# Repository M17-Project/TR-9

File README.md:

# TR-9
<p align='center'>

</p>

TR-9 is a handheld transceiver (HT) for the M17 standard. Its specification can be found [here](https://github.com/sp5wwp/M17_spec).
This repo contains KiCAD schematics and gerber files. 

The firmware source code has been moved to [M17-project/TR-9_firmware](https://github.com/m17-project/TR-9_firmware).
The codeplug example has been moved to [TR-9_Codeplug](https://github.com/M17-Project/codeplug)

# Capabilities
The TR-9 Radio will be capable of the following:
* UHF band (420 MHz - 450 MHz)
* Digital Voice ([M17 Codec](https://docs.m17project.org))
* FM Voice
* APRS via 1200 bps Packet (AX.25)
* Short text messaging (SMS-like)
* Optional Wi-Fi and GPS modules

# Hardware  
The heart of TR-9 is STM32F777VI microcontroller. The handheld also contains:  
*  a **DEM 128128A1 TMH-PWN** 1.44" 128x128px TFT display  
*  an **ESP8266-12F** WiFi module  
*  an **ADF7021** chip for the RF  
*  an **LSM9DS1** 9DoF sensor  
*  a USB-micro connector for firmware update (so-called *DFU mode*)  
*  a microSD card slot for codeplug and storage  
*  a connector for a GNSS module  
*  a Kenwood connector for external MIC/SPK  

RF output level can be regulated by the software. The maximum power output is 3 watts. The radio can work with both analog and digital modulation.  

# Software
M17 standard was designed having [Codec2](https://github.com/drowe67/codec2) vocoder in mind. TR-9 takes advantage of STM's internal Advanced Encryption Standard (AES) hardware for optional end-to-end encryption. There is a possibility of using other block ciphers and scrambling.  

## Pinouts

Mainboard SWD/STLink: [GND, 3v3, CLK, DIO, RST], square pad is Pin 1 and therefore GND.

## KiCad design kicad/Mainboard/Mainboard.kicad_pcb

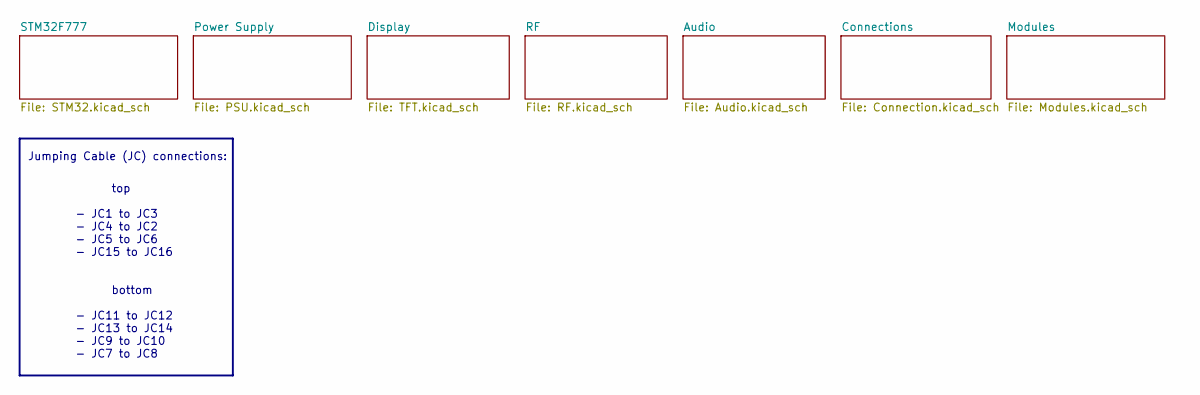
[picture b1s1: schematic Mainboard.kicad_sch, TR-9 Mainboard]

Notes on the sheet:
top - JC1 to JC3 - JC4 to JC2 - JC5 to JC6 - JC15 to JC16 bottom - JC11 to JC12 - JC13 to JC14 - JC9 to JC10 - JC7 to JC8
Jumping Cable (JC) connections:

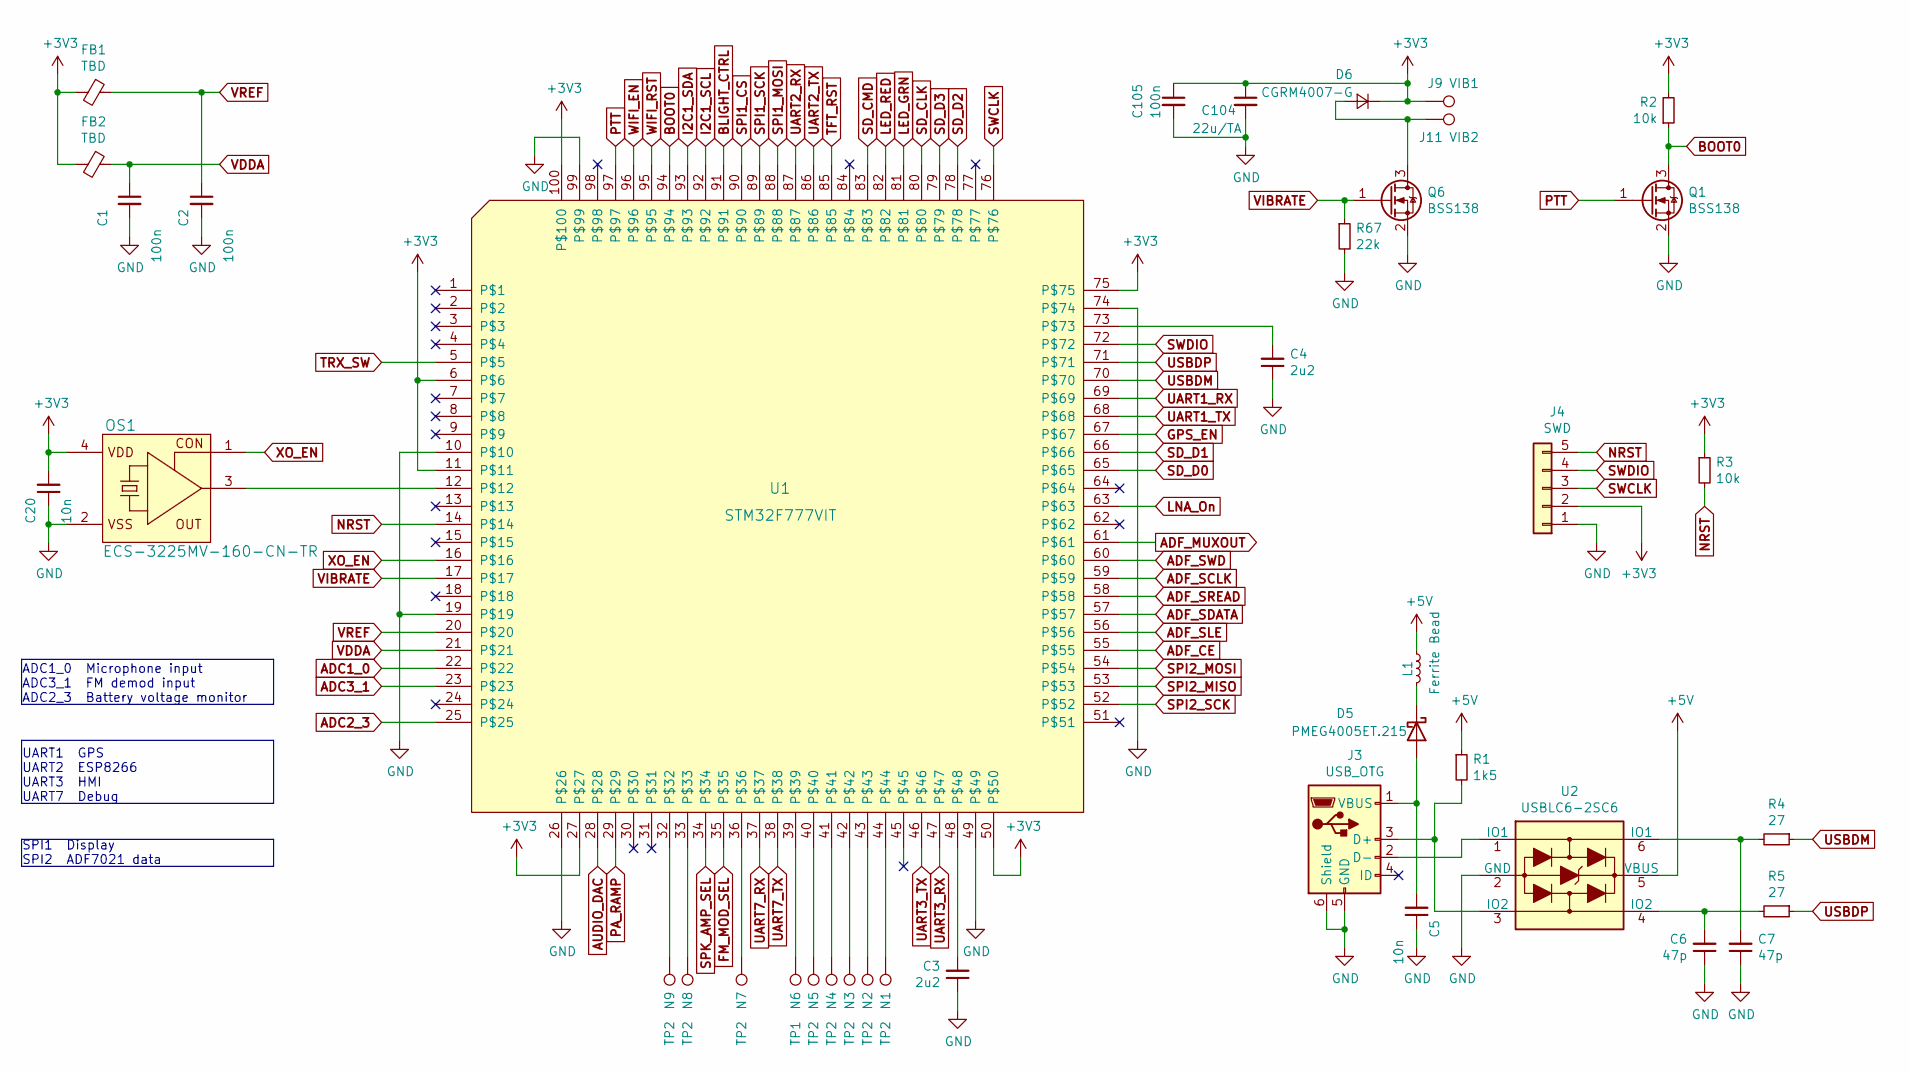
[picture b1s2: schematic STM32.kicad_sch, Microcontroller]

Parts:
C1, C2, C105: 100n; C_0603_1608Metric; Voltage 50; Tolerance 10
C3, C4: 2u2; C_0603_1608Metric; Tolerance 10; Voltage 50
C5: 10n; C_0603_1608Metric; Voltage 50; Tolerance 10
C6, C7: 47p; C_0603_1608Metric; Tolerance 5; Voltage 50
C20: 10n; C_0603_1608Metric; Tolerance 10; Voltage 50
C104: 22u/TA; CP_EIA-3216-18_Kemet-A; Tolerance 10; Voltage 10; Partno TAJA226K006RNJV
D5: PMEG4005ET.215
D6: CGRM4007-G; D_SOD-123
FB1, FB2: TBD; L_0603_1608Metric
J3: USB_OTG; USB_Mini-B_Wuerth_65100516121_Horizontal
J4: SWD; PinHeader_1x05_P1.27mm_Vertical
J9: VIB1; TestPoint_Pad_2.0x2.0mm
J11: VIB2; TestPoint_Pad_2.0x2.0mm
L1: Ferrite Bead; L_0603_1608Metric; Partno Fair-Rite 2506032217Y2
N1, N2, N3, N4, N5, N7, N8, N9: TP2; TestPoint_Pad_D1.0mm
N6: TP1; TestPoint_Pad_D1.0mm
OS1: ECS-3225MV-160-CN-TR; ECS-3225-MV-160-CN-TR
Q1, Q6: BSS138; SOT-23
R1: 1k5; R_0603_1608Metric; Tolerance 5
R2, R3: 10k; R_0603_1608Metric; Tolerance 5
R4, R5: 27; R_0603_1608Metric; Tolerance 5
R67: 22k; R_0603_1608Metric; Tolerance 5
U1: STM32F777VIT; LQFP-100_14x14mm_P0.5mm
U2: USBLC6-2SC6; SOT-23-6

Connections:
+5V: L1.1, R1.1, U2.5 (VBUS); also elsewhere on the board
ADC1_0: U1.22; also elsewhere on the board
ADC2_3: U1.25; also elsewhere on the board
ADC3_1: U1.23; also elsewhere on the board
ADF_CE: U1.55; also elsewhere on the board
ADF_MUXOUT: U1.61; also elsewhere on the board
ADF_SCLK: U1.59; also elsewhere on the board
ADF_SDATA: U1.57; also elsewhere on the board
ADF_SLE: U1.56; also elsewhere on the board
ADF_SREAD: U1.58; also elsewhere on the board
ADF_SWD: U1.60; also elsewhere on the board
AUDIO_DAC: U1.28; also elsewhere on the board
BLIGHT_CTRL: U1.91; also elsewhere on the board
BOOT0: Q1.3 (D), R2.1, U1.94
FM_MOD_SEL: U1.35; also elsewhere on the board
GPS_EN: U1.67; also elsewhere on the board
I2C1_SCL: U1.92; also elsewhere on the board
I2C1_SDA: U1.93; also elsewhere on the board
LED_GRN: U1.81; also elsewhere on the board
LED_RED: U1.82; also elsewhere on the board
LNA_On: U1.63; also elsewhere on the board
NRST: J4.5, R3.2, U1.14
unnamed: C3.2, U1.48
unnamed: C4.2, U1.73
unnamed: C5.2, D5.2 (A), J3.1 (VBUS)
unnamed: C6.2, R5.2, U2.4 (IO2)
unnamed: C7.2, R4.2, U2.6 (IO1)
unnamed: D5.1 (K), L1.2
unnamed: D6.2 (A), J11.1, Q6.3 (D)
unnamed: J3.2 (D-), U2.1 (IO1)
unnamed: J3.3 (D+), R1.2, U2.3 (IO2)
unnamed: N1.1, U1.44
unnamed: N2.1, U1.43
unnamed: N3.1, U1.42
unnamed: N4.1, U1.41
unnamed: N5.1, U1.40
unnamed: N6.1, U1.39
unnamed: N7.1, U1.36
unnamed: N8.1, U1.33
unnamed: N9.1, U1.32
unnamed: OS1.3 (OUT), U1.12
PA_RAMP: U1.29; also elsewhere on the board
PTT: Q1.1 (G), U1.97; also elsewhere on the board
SD_CLK: U1.80; also elsewhere on the board
SD_CMD: U1.83; also elsewhere on the board
SD_D0: U1.65; also elsewhere on the board
SD_D1: U1.66; also elsewhere on the board
SD_D2: U1.78; also elsewhere on the board
SD_D3: U1.79; also elsewhere on the board
SPI1_CS: U1.90; also elsewhere on the board
SPI1_MOSI: U1.88; also elsewhere on the board
SPI1_SCK: U1.89; also elsewhere on the board
SPI2_MISO: U1.53; also elsewhere on the board
SPI2_MOSI: U1.54; also elsewhere on the board
SPI2_SCK: U1.52; also elsewhere on the board
SPK_AMP_SEL: U1.34; also elsewhere on the board
SWCLK: J4.3, U1.76
SWDIO: J4.4, U1.72
TFT_RST: U1.85; also elsewhere on the board
TRX_SW: U1.5; also elsewhere on the board
UART1_RX: U1.69; also elsewhere on the board
UART1_TX: U1.68; also elsewhere on the board
UART2_RX: U1.87; also elsewhere on the board
UART2_TX: U1.86; also elsewhere on the board
UART3_RX: U1.47; also elsewhere on the board
UART3_TX: U1.46
UART7_RX: U1.37; also elsewhere on the board
UART7_TX: U1.38; also elsewhere on the board
USBDM: R4.1, U1.70
USBDP: R5.1, U1.71
VDDA: C1.1, FB2.1, U1.21
VIBRATE: Q6.1 (G), R67.1, U1.17
VREF: C2.1, FB1.1, U1.20
WIFI_EN: U1.96; also elsewhere on the board
WIFI_RST: U1.95; also elsewhere on the board
XO_EN: OS1.1 (CON), U1.16

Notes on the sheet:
UART1 GPS UART2 ESP8266 UART3 HMI UART7 Debug
ADC1_0 Microphone input ADC3_1 FM demod input ADC2_3 Battery voltage monitor
SPI1 Display SPI2 ADF7021 data

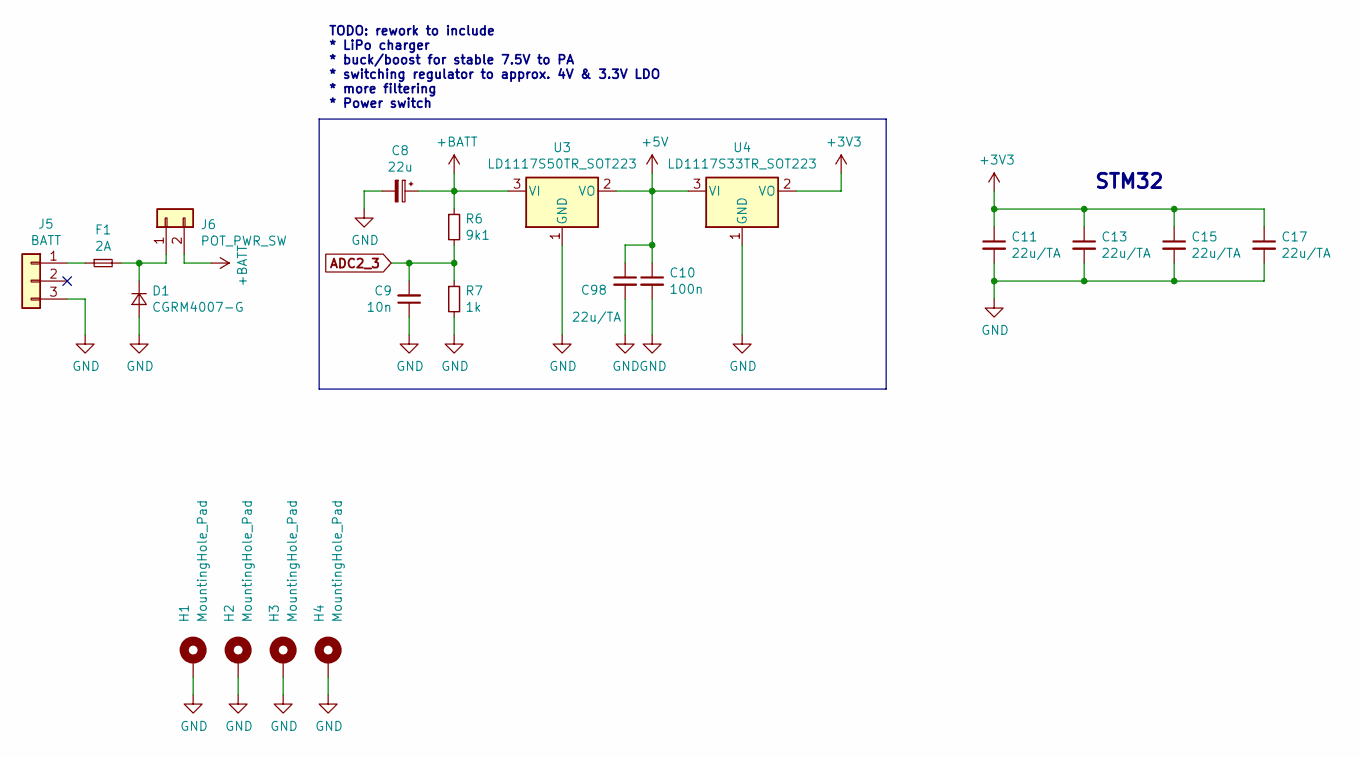
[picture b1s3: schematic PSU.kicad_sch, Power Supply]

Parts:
C8: 22u; CP_Radial_D4.0mm_P2.00mm; Tolerance 10; Voltage 25; Partno TAJA226K006RNJV
C9: 10n; C_0603_1608Metric; Tolerance 10; Voltage 50
C10: 100n; C_0603_1608Metric; Voltage 50; Tolerance 10
C11, C13, C15, C17, C98: 22u/TA; CP_EIA-3216-18_Kemet-A; Tolerance 10; Voltage 10; Partno TAJA226K006RNJV
D1: CGRM4007-G; D_SOD-123
F1: 2A; Fuse_1812_4532Metric
H1, H2, H3, H4: MountingHole_Pad; MountingHole_2.2mm_M2_ISO14580_Pad
J5: BATT; PinHeader_1x03_P1.27mm_Vertical
J6: POT_PWR_SW; PinHeader_1x02_P1.27mm_Vertical
R6: 9k1; R_0603_1608Metric; Tolerance 5
R7: 1k; R_0603_1608Metric; Tolerance 5
U3: LD1117S50TR_SOT223; SOT-223-3_TabPin2
U4: LD1117S33TR_SOT223; SOT-223-3_TabPin2

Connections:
+5V: C10.1, C98.1, U3.2 (VO), U4.3 (VI); also elsewhere on the board
+BATT: C8.1, J6.2, R6.1, U3.3 (VI); also elsewhere on the board
ADC2_3: C9.2, R6.2, R7.1; also elsewhere on the board
unnamed: D1.1 (K), F1.2, J6.1
unnamed: F1.1, J5.1

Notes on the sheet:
STM32
TODO: rework to include * LiPo charger * buck/boost for stable 7.5V to PA * switching regulator to approx. 4V & 3.3V LDO * more filtering * Power switch

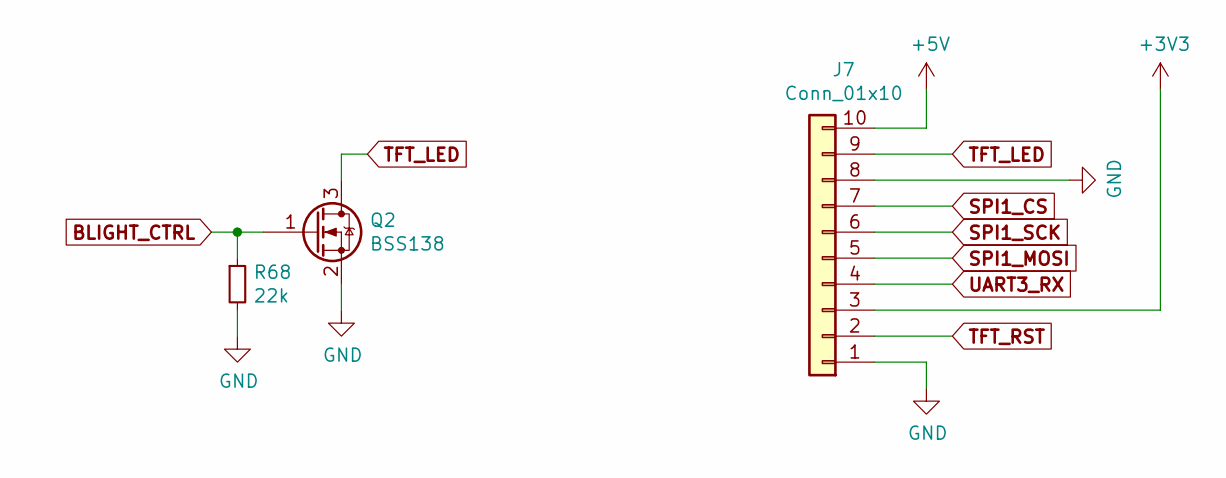
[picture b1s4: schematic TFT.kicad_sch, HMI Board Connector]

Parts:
J7: Conn_01x10; Hirose_FH12-10S-0.5SH_1x10-1MP_P0.50mm_Horizontal
Q2: BSS138; SOT-23
R68: 22k; R_0603_1608Metric; Tolerance 5

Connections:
+5V: J7.10; also elsewhere on the board
BLIGHT_CTRL: Q2.1 (G), R68.1; also elsewhere on the board
SPI1_CS: J7.7; also elsewhere on the board
SPI1_MOSI: J7.5; also elsewhere on the board
SPI1_SCK: J7.6; also elsewhere on the board
TFT_LED: J7.9, Q2.3 (D)
TFT_RST: J7.2; also elsewhere on the board
UART3_RX: J7.4; also elsewhere on the board

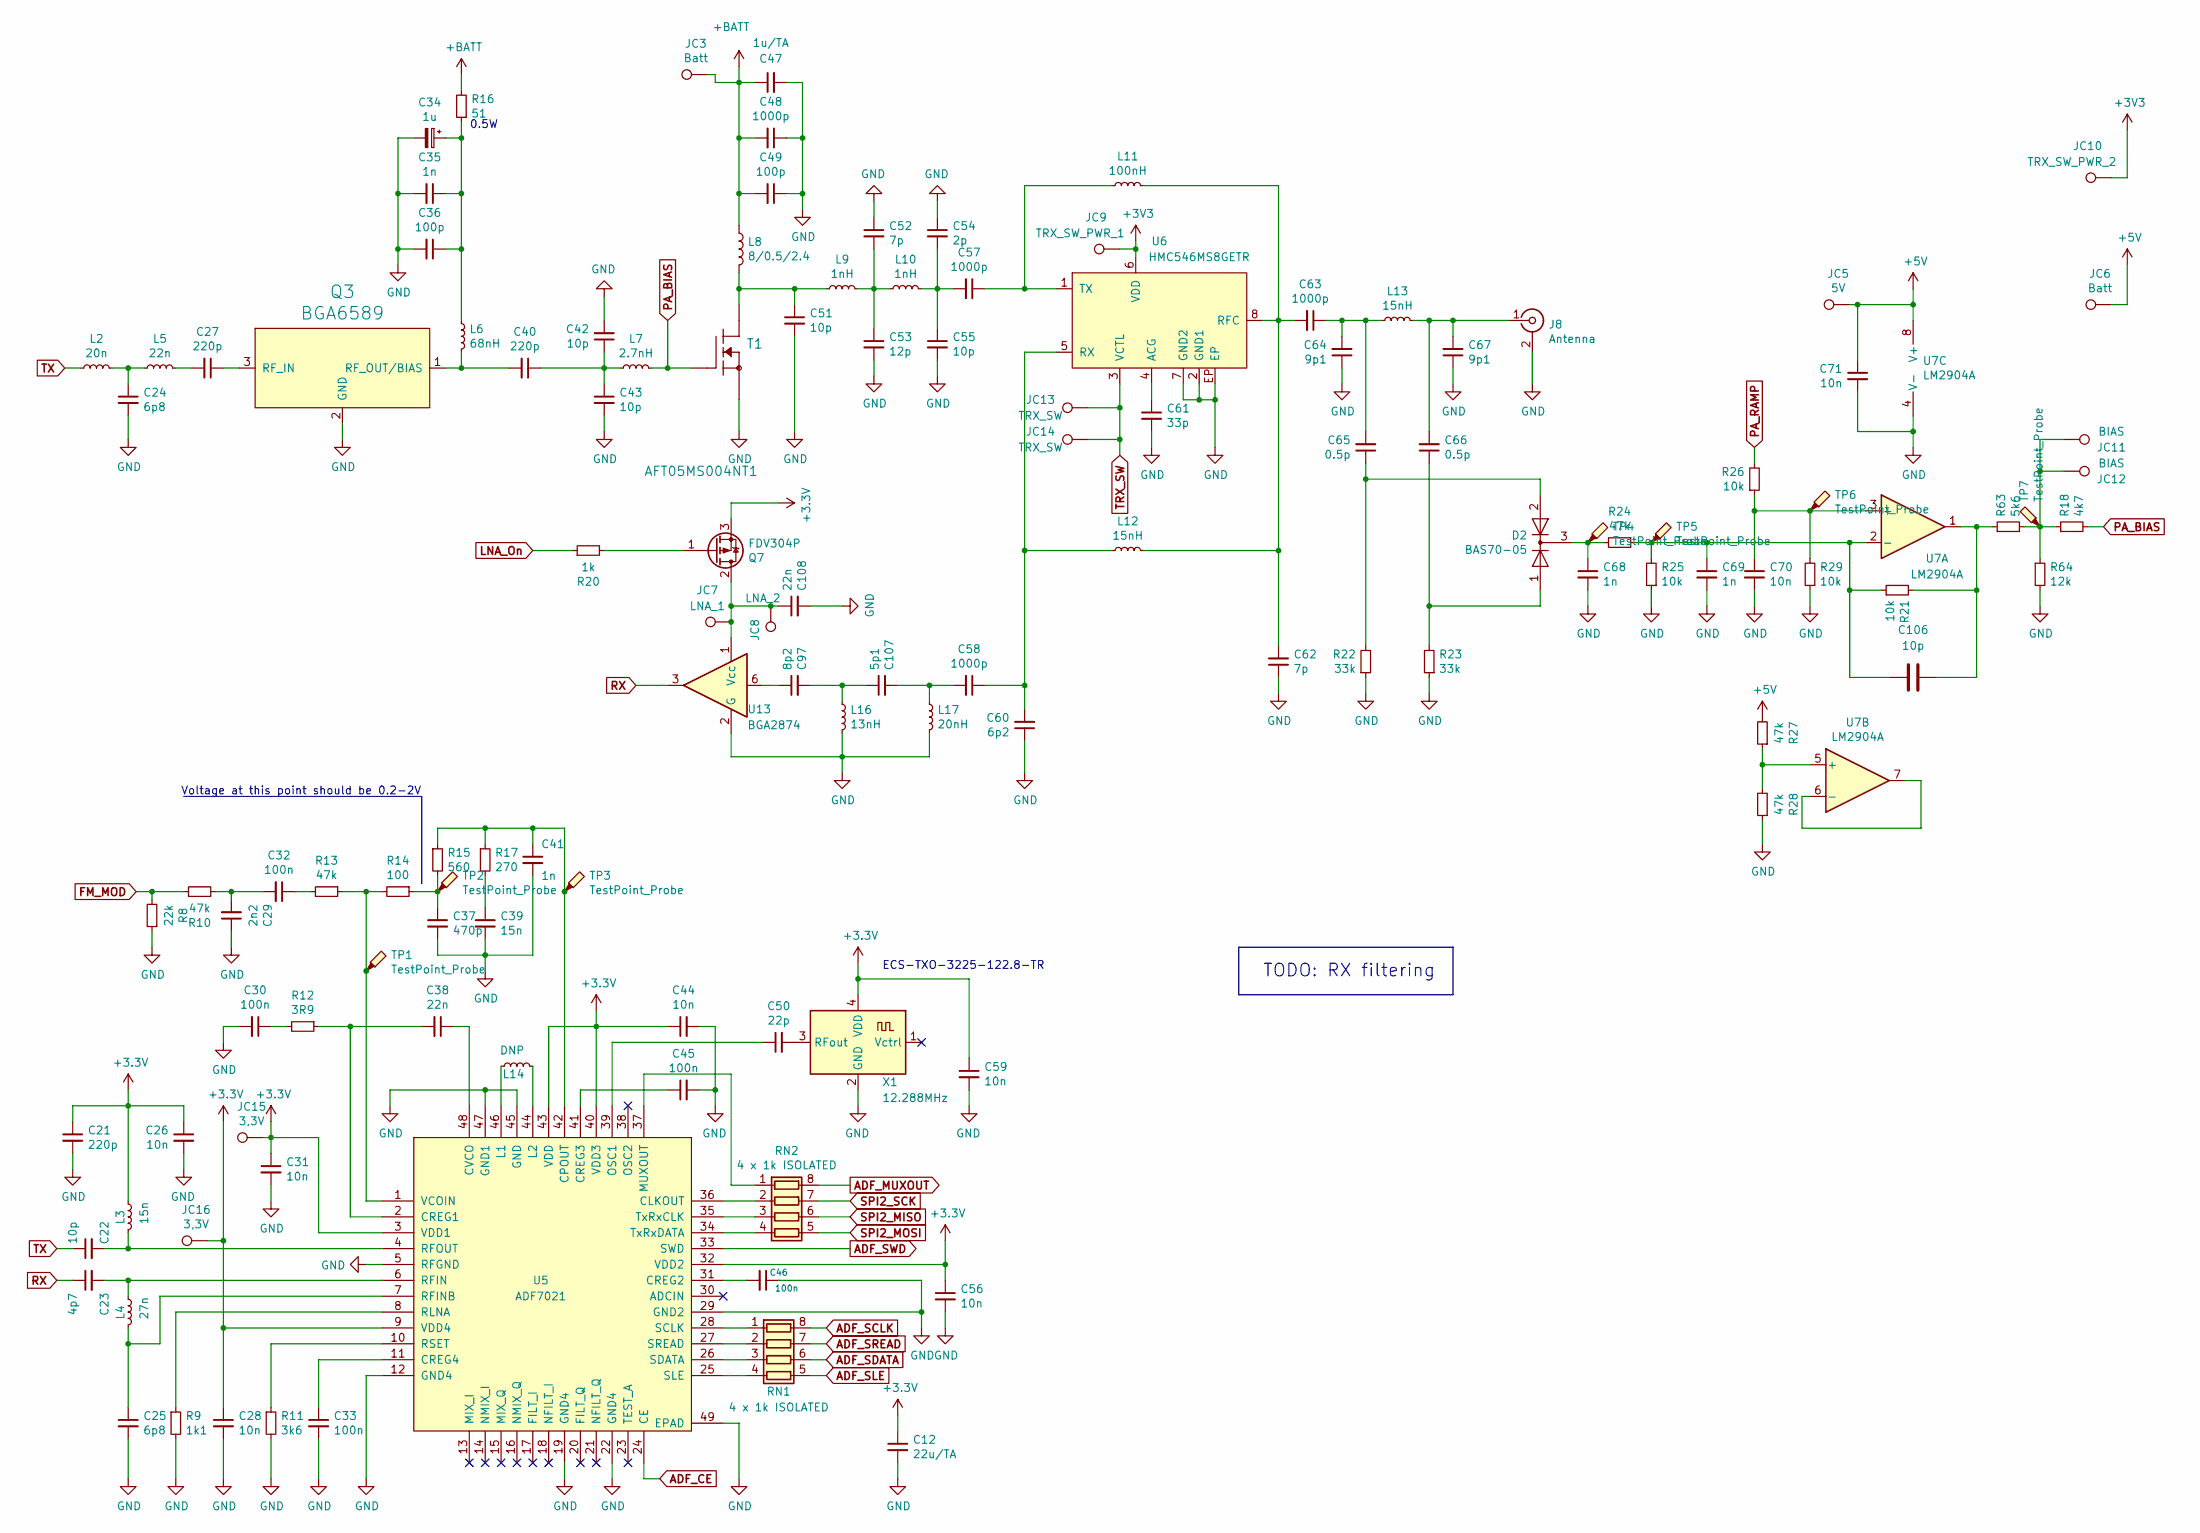
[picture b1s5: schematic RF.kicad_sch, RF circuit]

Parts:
C12: 22u/TA; CP_EIA-3216-18_Kemet-A; Tolerance 10; Voltage 10; Partno TAJA226K006RNJV
C21, C27, C40: 220p; C_0603_1608Metric; Voltage 50; Tolerance 5
C22, C42, C43, C51, C55: 10p; C_0603_1608Metric; Voltage 50; Tolerance 5
C23: 4p7; C_0603_1608Metric; Voltage 50; Tolerance 5
C24, C25: 6p8; C_0603_1608Metric; Voltage 50; Tolerance 5
C26, C28, C31, C44, C56, C59, C70, C71: 10n; C_0603_1608Metric; Tolerance 10; Voltage 50
C29: 2n2; C_0603_1608Metric; Voltage 50; Tolerance 5
C30, C32, C33, C45, C46: 100n; C_0603_1608Metric; Voltage 50; Tolerance 10
C34: 1u; C_0603_1608Metric; Voltage 50; Tolerance 10
C35, C41, C68, C69: 1n; C_0603_1608Metric; Voltage 50; Tolerance 10
C36, C49: 100p; C_0603_1608Metric; Voltage 50; Tolerance 5
C37: 470p; C_0603_1608Metric; Voltage 50; Tolerance 5
C38, C108: 22n; C_0603_1608Metric; Voltage 50; Tolerance 10
C39: 15n; C_0603_1608Metric; Voltage 50; Tolerance 10
C47: 1u/TA; CP_EIA-3216-18_Kemet-A; Tolerance 10; Voltage 10; Partno T491A105M016AT
C48, C57, C58, C63: 1000p; C_0603_1608Metric; Voltage 50; Tolerance 5
C50: 22p; C_0603_1608Metric; Voltage 50; Tolerance 5
C52, C62: 7p; C_0603_1608Metric; Voltage 50; Tolerance 5
C53: 12p; C_0603_1608Metric; Voltage 50; Tolerance 5
C54: 2p; C_0603_1608Metric; Voltage 50; Tolerance 5
C60: 6p2; C_0603_1608Metric; Voltage 50; Tolerance 5
C61: 33p; C_0603_1608Metric; Voltage 50; Tolerance 5
C64, C67: 9p1; C_0603_1608Metric; Voltage 50; Tolerance 5
C65, C66: 0.5p; C_0603_1608Metric; Voltage 50; Tolerance 5
C97: 8p2; C_0603_1608Metric; Voltage 50; Tolerance 5
C106: 10p
C107: 5p1; C_0603_1608Metric; Voltage 50; Tolerance 5
D2: BAS70-05; SOT-23
J8: Antenna; SMA_Samtec_SMA-J-P-X-ST-EM1_EdgeMount
JC3, JC6: Batt; Pad1x3
JC5: 5V; Pad1x3
JC7: LNA_1; Pad1x3
JC8: LNA_2; Pad1x3
JC9: TRX_SW_PWR_1; Pad1x3
JC10: TRX_SW_PWR_2; Pad1x3
JC11, JC12: BIAS; Pad1x3
JC13, JC14: TRX_SW; Pad1x3
JC15, JC16: 3,3V; TestPoint_Pad_1.0x1.0mm
L2: 20n; L_0603_1608Metric
L3: 15n; L_0603_1608Metric
L4: 27n; L_0603_1608Metric
L5: 22n; L_0603_1608Metric
L6: 68nH; L_0603_1608Metric
L7: 2.7nH; L_0603_1608Metric
L8: 8/0.5/2.4; RF_Coil_v2_mirrored
L9, L10: 1nH; L_0603_1608Metric
L11: 100nH; L_0603_1608Metric
L12, L13: 15nH; L_0603_1608Metric
L14: DNP; L_0603_1608Metric
L16: 13nH; L_0603_1608Metric
L17: 20nH; L_0603_1608Metric
Q3: BGA6589
Q7: FDV304P; SOT-23
R8: 22k; R_0603_1608Metric; Tolerance 5
R9: 1k1; R_0603_1608Metric; Tolerance 5
R10, R13, R24, R27, R28: 47k; R_0603_1608Metric; Tolerance 5
R11: 3k6; R_0603_1608Metric; Tolerance 5
R12: 3R9; R_0603_1608Metric; Tolerance 5
R14: 100; R_0603_1608Metric; Tolerance 5
R15: 560; R_0603_1608Metric; Tolerance 5
R16: 51; R_0603_1608Metric; Tolerance 5
R17: 270; R_0603_1608Metric; Tolerance 5
R18: 4k7; R_0603_1608Metric; Tolerance 5
R20: 1k; R_0603_1608Metric
R21, R25, R26, R29: 10k; R_0603_1608Metric; Tolerance 5
R22, R23: 33k; R_0603_1608Metric; Tolerance 5
R63: 5k6; R_0603_1608Metric; Tolerance 5
R64: 12k; R_0603_1608Metric; Tolerance 5
RN1, RN2: 4 x 1k ISOLATED; R_Array_Concave_4x0603; Tolerance 5
T1: AFT05MS004NT1
TP1, TP2, TP3, TP4, TP5, TP6, TP7: TestPoint_Probe; TestPoint_Pad_D1.0mm
U5: ADF7021; LFCSP-48-1EP_7x7mm_P0.5mm_EP4.1x4.1mm_ThermalVias
U6: HMC546MS8GETR
U7: LM2904A; SO-8_3.9x4.9mm_P1.27mm
U13: BGA2874; SOT-363_SC-70-6
X1: 12.288MHz; ECS-TXO-3225

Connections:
+5V: C71.1, JC5.1, JC6.1, R27.2, U7.8 (V+); also elsewhere on the board
+BATT: C47.1, C48.2, C49.2, JC3.1, L8.1, R16.2; also elsewhere on the board
ADF_CE: U5.24 (CE); also elsewhere on the board
ADF_MUXOUT: RN2.8 (R1.2); also elsewhere on the board
ADF_SCLK: RN1.8 (R1.2); also elsewhere on the board
ADF_SDATA: RN1.6 (R3.2); also elsewhere on the board
ADF_SLE: RN1.5 (R4.2); also elsewhere on the board
ADF_SREAD: RN1.7 (R2.2); also elsewhere on the board
ADF_SWD: U5.33 (SWD); also elsewhere on the board
FM_MOD: R8.2, R10.1; also elsewhere on the board
LNA_On: R20.1; also elsewhere on the board
unnamed: C22.2, L3.2, U5.4 (RFOUT)
unnamed: C23.2, L4.1, U5.6 (RFIN)
unnamed: C24.1, L2.2, L5.1
unnamed: C25.1, L4.2, U5.7 (RFINB)
unnamed: C27.1, Q3.3 (RF_IN)
unnamed: C27.2, L5.2
unnamed: C29.2, C32.2, R10.2
unnamed: C30.1, R12.2
unnamed: C32.1, R13.2
unnamed: C33.1, U5.11 (CREG4)
unnamed: C34.1, C35.1, C36.1, L6.1, R16.1
unnamed: C37.1, R14.1, R15.2, TP2.1
unnamed: C38.1, U5.48 (CVCO)
unnamed: C38.2, R12.1, U5.2 (CREG1)
unnamed: C39.1, R17.2
unnamed: C40.1, C42.1, C43.1, L7.1
unnamed: C40.2, L6.2, Q3.1 (RF_OUT/BIAS)
unnamed: C41.1, R15.1, R17.1, TP3.1, U5.42 (CPOUT)
unnamed: C45.1, U5.41 (CREG3)
unnamed: C46.2, U5.31 (CREG2)
unnamed: C50.1, U5.39 (OSC1)
unnamed: C50.2, X1.3 (RFout)
unnamed: C51.1, L8.2, L9.1, T1.D
unnamed: C52.2, C53.1, L9.2, L10.1
unnamed: C54.2, C55.1, C57.2, L10.2
unnamed: C57.1, L11.1, U6.1 (TX)
unnamed: C58.1, C60.2, L12.1, U6.5 (RX)
unnamed: C61.1, U6.4 (ACG)
unnamed: C62.2, C63.2, L11.2, L12.2, U6.8 (RFC)
unnamed: C63.1, C64.2, C65.2, L13.1
unnamed: C65.1, D2.2 (A), R22.2
unnamed: C66.1, D2.1 (A), R23.2
unnamed: C66.2, C67.2, J8.1 (In), L13.2
unnamed: C68.1, D2.3 (K), R24.2, TP4.1
unnamed: C70.1, R26.1, R29.2, TP6.1, U7.3 (+)
unnamed: C97.1, U13.6
unnamed: C106.1, R21.2, R63.1, U7.1
unnamed: C69.1, C106.2, R21.1, R24.1, R25.2, TP5.1, U7.2 (-)
unnamed: C97.2, C107.1, L16.1
unnamed: C58.2, C107.2, L17.1
unnamed: C108.1, JC7.1, JC8.1, Q7.2 (D), U13.1 (Vcc)
unnamed: JC11.1, JC12.1, R18.1, R63.2, R64.1, TP7.1
unnamed: L14.1, U5.46 (L1)
unnamed: L14.2, U5.44 (L2)
unnamed: Q7.1 (G), R20.2
unnamed: R9.1, U5.8 (RLNA)
unnamed: R11.1, U5.10 (RSET)
unnamed: R13.1, R14.2, TP1.1, U5.1 (VCOIN)
unnamed: R27.1, R28.2, U7.5 (+)
unnamed: RN1.1 (R1.1), U5.28 (SCLK)
unnamed: RN1.2 (R2.1), U5.27 (SREAD)
unnamed: RN1.3 (R3.1), U5.26 (SDATA)
unnamed: RN1.4 (R4.1), U5.25 (SLE)
unnamed: RN2.1 (R1.1), U5.37 (MUXOUT)
unnamed: RN2.2 (R2.1), U5.36 (CLKOUT)
unnamed: RN2.3 (R3.1), U5.35 (TxRxCLK)
unnamed: RN2.4 (R4.1), U5.34 (TxRxDATA)
unnamed: U7.6 (-), U7.7
PA_BIAS: L7.2, R18.2, T1.G
PA_RAMP: R26.2; also elsewhere on the board
RX: C23.1, U13.3
SPI2_MISO: RN2.6 (R3.2); also elsewhere on the board
SPI2_MOSI: RN2.5 (R4.2); also elsewhere on the board
SPI2_SCK: RN2.7 (R2.2); also elsewhere on the board
TRX_SW: JC13.1, JC14.1, U6.3 (VCTL); also elsewhere on the board
TX: C22.1, L2.1

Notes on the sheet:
Voltage at this point should be 0.2-2V
TODO: RX filtering
ECS-TXO-3225-122.8-TR
0.5W

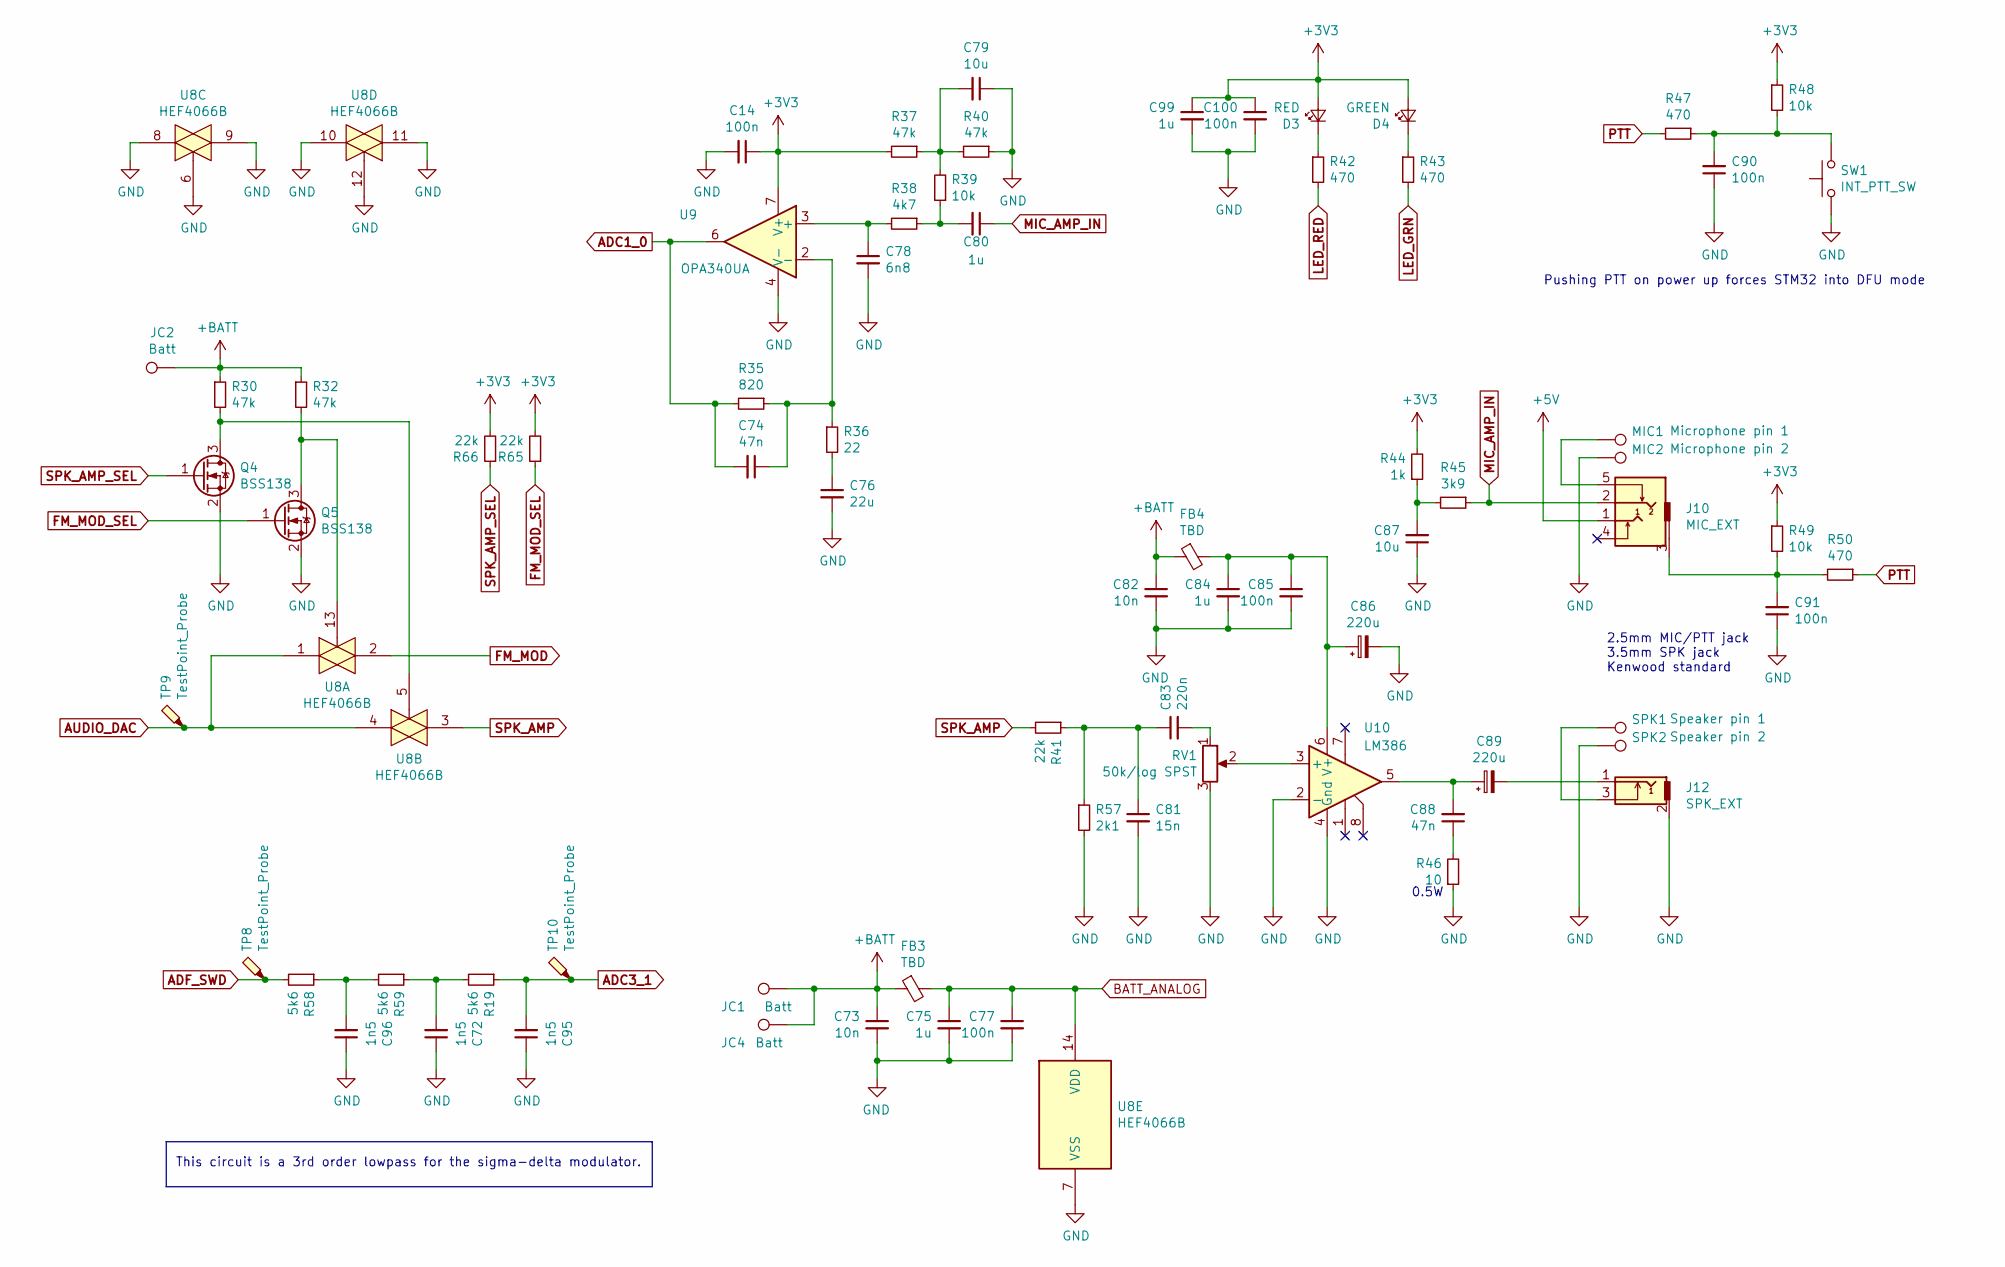
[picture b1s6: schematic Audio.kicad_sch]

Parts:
C14, C77, C85, C90, C91, C100: 100n; C_0603_1608Metric; Voltage 50; Tolerance 10
C72, C95, C96: 1n5; C_0603_1608Metric; Voltage 50; Tolerance 10
C73, C82: 10n; C_0603_1608Metric; Tolerance 10; Voltage 50
C74, C88: 47n; C_0603_1608Metric; Voltage 50; Tolerance 10
C75, C80, C84, C99: 1u; C_0603_1608Metric; Voltage 50; Tolerance 10
C76: 22u; C_0603_1608Metric; Voltage 10; Tolerance 10
C78: 6n8; C_0603_1608Metric; Voltage 50; Tolerance 10
C79, C87: 10u; C_0603_1608Metric; Voltage 10; Tolerance 10
C81: 15n; C_0603_1608Metric; Voltage 50; Tolerance 10
C83: 220n; C_0603_1608Metric; Voltage 50; Tolerance 10
C86, C89: 220u; CP_EIA-7343-31_Kemet-D; Tolerance 10; Voltage 10; Partno TCJD227M016R0050
D3: RED; D_0603_1608Metric
D4: GREEN; D_0603_1608Metric
FB3, FB4: TBD; L_0603_1608Metric
J10: MIC_EXT
J12: SPK_EXT
JC1, JC2, JC4: Batt; Pad1x3
MIC1: Microphone pin 1; TestPoint_Pad_2.0x2.0mm
MIC2: Microphone pin 2; TestPoint_Pad_2.0x2.0mm
Q4, Q5: BSS138; SOT-23
R19, R58, R59: 5k6; R_0603_1608Metric; Tolerance 5
R30, R32, R37, R40: 47k; R_0603_1608Metric; Tolerance 5
R35: 820; R_0603_1608Metric; Tolerance 5
R36: 22; R_0603_1608Metric; Tolerance 5
R38: 4k7; R_0603_1608Metric; Tolerance 5
R39, R48, R49: 10k; R_0603_1608Metric; Tolerance 5
R41, R65, R66: 22k; R_0603_1608Metric; Tolerance 5
R42, R43, R47, R50: 470; R_0603_1608Metric; Tolerance 5
R44: 1k; R_0603_1608Metric; Tolerance 5
R45: 3k9; R_0603_1608Metric; Tolerance 5
R46: 10; R_0603_1608Metric; Tolerance 5
R57: 2k1; R_0603_1608Metric; Tolerance 5
RV1: 50k/log SPST; PinHeader_1x03_P1.27mm_Vertical; Partno Alps RK0971111Z32
SPK1: Speaker pin 1; TestPoint_Pad_2.0x2.0mm
SPK2: Speaker pin 2; TestPoint_Pad_2.0x2.0mm
SW1: INT_PTT_SW; SW_Push_1P1T_NO_CK_KMR2
TP8, TP9, TP10: TestPoint_Probe; TestPoint_Pad_D1.0mm
U8: HEF4066B; SOIC-14_3.9x8.7mm_P1.27mm
U9: OPA340UA; SO-8_3.9x4.9mm_P1.27mm
U10: LM386; SOIC-8_3.9x4.9mm_P1.27mm

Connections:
+5V: J10.1; also elsewhere on the board
+BATT: C73.1, C82.1, FB3.1, FB4.1, JC1.1, JC2.1, JC4.1, R30.1, R32.1; also elsewhere on the board
ADC1_0: C74.2, R35.2, U9.6; also elsewhere on the board
ADC3_1: C95.2, R19.1, TP10.1; also elsewhere on the board
ADF_SWD: R58.2, TP8.1; also elsewhere on the board
AUDIO_DAC: TP9.1, U8.1, U8.4; also elsewhere on the board
BATT_ANALOG: C75.1, C77.1, FB3.2, U8.14 (VDD)
FM_MOD: U8.2; also elsewhere on the board
FM_MOD_SEL: Q5.1 (G), R65.1; also elsewhere on the board
LED_GRN: R43.2; also elsewhere on the board
LED_RED: R42.2; also elsewhere on the board
MIC_AMP_IN: C80.1, J10.2, R45.1
unnamed: C72.2, R19.2, R59.1
unnamed: C74.1, R35.1, R36.1, U9.2 (-)
unnamed: C76.1, R36.2
unnamed: C78.1, R38.2, U9.3 (+)
unnamed: C79.2, R37.1, R39.2, R40.2
unnamed: C80.2, R38.1, R39.1
unnamed: C81.1, C83.1, R41.1, R57.1
unnamed: C83.2, RV1.1
unnamed: C84.1, C85.1, C86.1, FB4.2, U10.6 (V+)
unnamed: C87.2, R44.1, R45.2
unnamed: C88.1, R46.2
unnamed: C88.2, C89.1, U10.5
unnamed: C89.2, J12.1
unnamed: C91.2, J10.3, R49.2, R50.2
unnamed: C96.2, R58.1, R59.2
unnamed: D3.1 (K), R42.1
unnamed: D4.1 (K), R43.1
unnamed: J10.5, MIC1.1
unnamed: J12.3, SPK1.1
unnamed: Q4.3 (D), R30.2, U8.5
unnamed: Q5.3 (D), R32.2, U8.13
unnamed: RV1.2, U10.3 (+)
PTT: R47.2, R50.1; also elsewhere on the board
SPK_AMP: R41.2, U8.3
SPK_AMP_SEL: Q4.1 (G), R66.1; also elsewhere on the board

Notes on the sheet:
This circuit is a 3rd order lowpass for the sigma-delta modulator.
2.5mm MIC/PTT jack 3.5mm SPK jack Kenwood standard
Pushing PTT on power up forces STM32 into DFU mode
0.5W

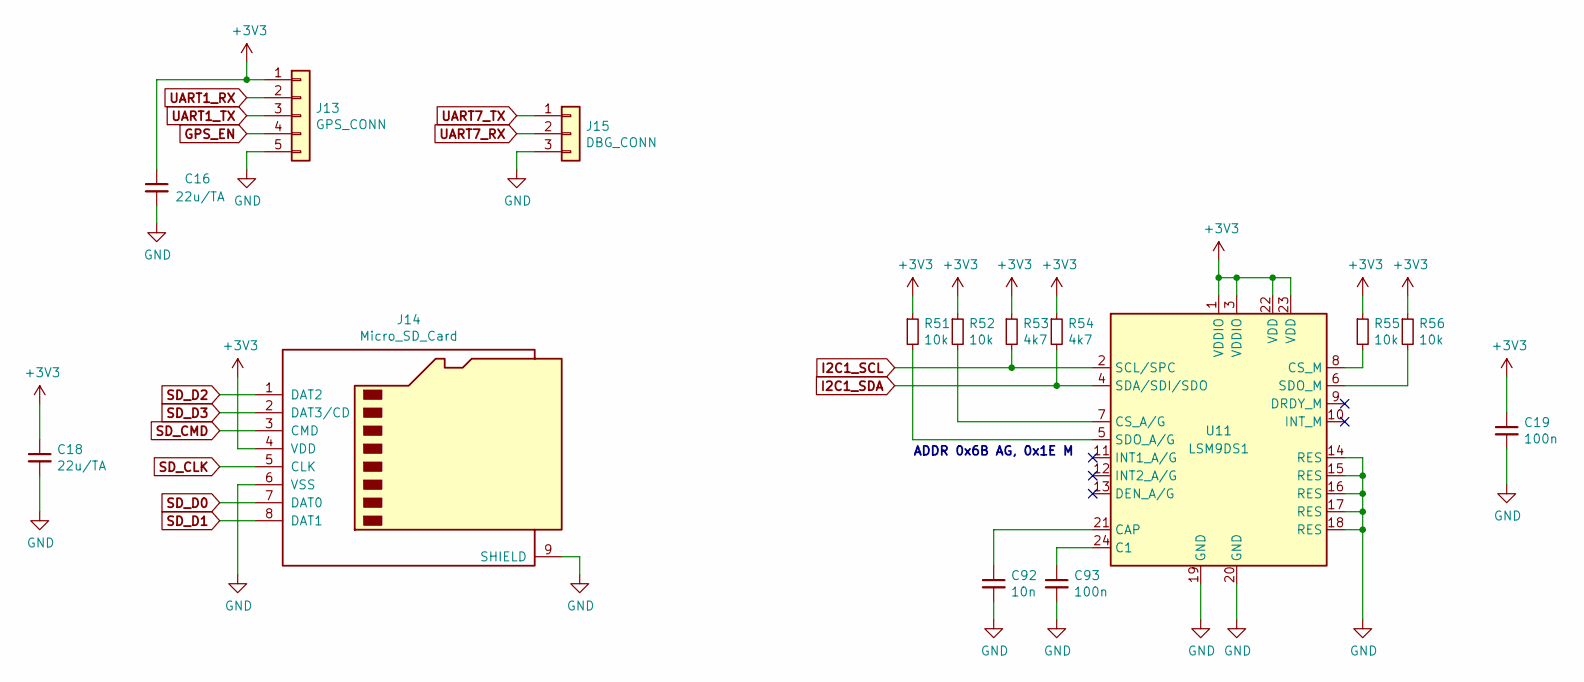
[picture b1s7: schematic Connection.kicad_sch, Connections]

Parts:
C16, C18: 22u/TA; CP_EIA-3216-18_Kemet-A; Tolerance 10; Voltage 10; Partno TAJA226K006RNJV
C19, C93: 100n; C_0603_1608Metric; Voltage 50; Tolerance 10
C92: 10n; C_0603_1608Metric; Tolerance 10; Voltage 50
J13: GPS_CONN; PinHeader_1x05_P1.27mm_Vertical
J14: Micro_SD_Card; microSD; Partno AdamTech MCSP-Q1-08-A-SG
J15: DBG_CONN; PinHeader_1x03_P1.27mm_Vertical
R51, R52, R55, R56: 10k; R_0603_1608Metric; Tolerance 5
R53, R54: 4k7; R_0603_1608Metric; Tolerance 5
U11: LSM9DS1; LGA-24L_3x3.5mm_P0.43mm

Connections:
GPS_EN: J13.4; also elsewhere on the board
I2C1_SCL: R53.2, U11.2 (SCL/SPC); also elsewhere on the board
I2C1_SDA: R54.2, U11.4 (SDA/SDI/SDO); also elsewhere on the board
unnamed: C92.1, U11.21 (CAP)
unnamed: C93.1, U11.24 (C1)
unnamed: R51.2, U11.5 (SDO_A/G)
unnamed: R52.2, U11.7 (CS_A/G)
unnamed: R55.2, U11.8 (CS_M)
unnamed: R56.2, U11.6 (SDO_M)
SD_CLK: J14.5 (CLK); also elsewhere on the board
SD_CMD: J14.3 (CMD); also elsewhere on the board
SD_D0: J14.7 (DAT0); also elsewhere on the board
SD_D1: J14.8 (DAT1); also elsewhere on the board
SD_D2: J14.1 (DAT2); also elsewhere on the board
SD_D3: J14.2 (DAT3/CD); also elsewhere on the board
UART1_RX: J13.2; also elsewhere on the board
UART1_TX: J13.3; also elsewhere on the board
UART7_RX: J15.2; also elsewhere on the board
UART7_TX: J15.1; also elsewhere on the board

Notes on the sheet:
ADDR 0x6B AG, 0x1E M

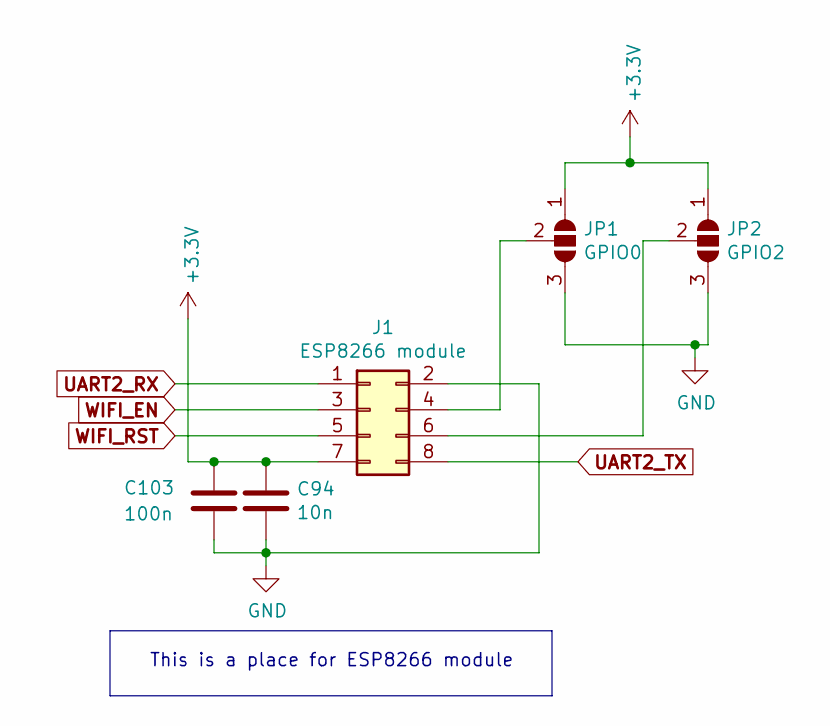
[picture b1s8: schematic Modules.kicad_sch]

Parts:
C94: 10n; C_0603_1608Metric; Tolerance 10; Voltage 50
C103: 100n; C_0603_1608Metric; Voltage 50; Tolerance 10
J1: ESP8266 module; PinHeader_2x04_P2.54mm_Vertical
JP1: GPIO0; SolderJumper-3_P1.3mm_Open_RoundedPad1.0x1.5mm
JP2: GPIO2; SolderJumper-3_P1.3mm_Open_RoundedPad1.0x1.5mm

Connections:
unnamed: J1.4, JP1.2 (C)
unnamed: J1.6, JP2.2 (C)
UART2_RX: J1.1; also elsewhere on the board
UART2_TX: J1.8; also elsewhere on the board
WIFI_EN: J1.3; also elsewhere on the board
WIFI_RST: J1.5; also elsewhere on the board

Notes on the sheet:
This is a place for ESP8266 module

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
